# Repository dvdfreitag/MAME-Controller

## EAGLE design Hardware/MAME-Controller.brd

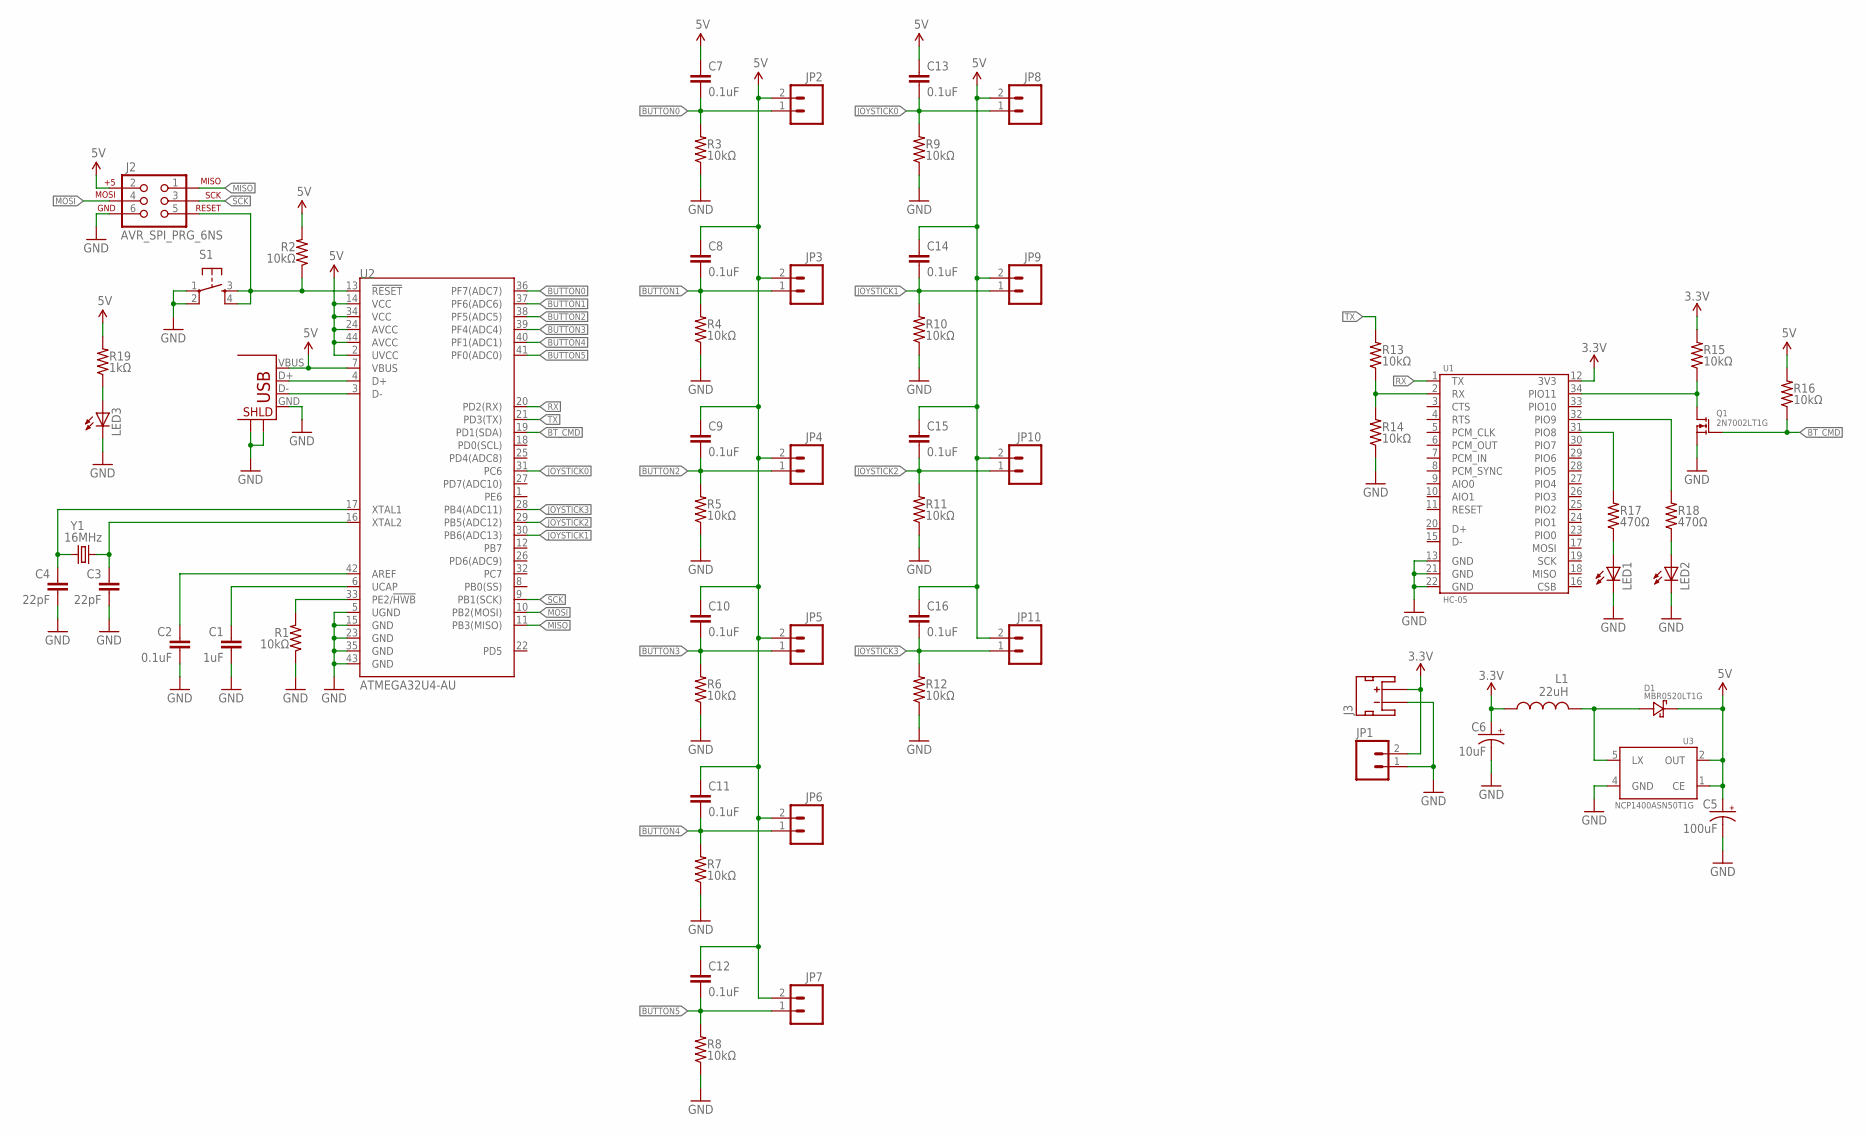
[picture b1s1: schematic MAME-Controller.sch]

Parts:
C1: 1uF; 0805
C2, C7, C8, C9, C10, C11, C12, C13, C14, C15, C16: 0.1uF; 0805
C3, C4: 22pF; 0805
C5: 100uF; CAP_POL-0.35X0.5
C6: 10uF; EIA3216-KIT
D1: MBR0520LT1G; SOD123
J1: USB+SHIELD; USB-B-PTH
J2: AVR_SPI_PRG_6NS; 2X3-NS
J3: JST_2MM_MALE; JST-2-SMD
JP1: M02PTH; 1X02
JP2, JP3, JP4, JP5, JP6, JP7, JP8, JP9, JP10, JP11: M02POLAR; MOLEX-1X2
L1: 22uH; 0805
LED1, LED2, LED3: LED-FKIT-1206; FKIT-LED-1206
Q1: 2N7002LT1G; SOT23
R1, R2, R3, R4, R5, R6, R7, R8, R9, R10, R11, R12, R13, R14, R15, R16: 10kΩ; 0805
R17, R18: 470Ω; 0805
R19: 1kΩ; 0805
S1: TAC_SWITCHSMD; TACTILE_SWITCH_SMD
U1: HC-05
U2: ATMEGA32U4-AU; TQFP-44
U3: NCP1400ASN50T1G; SOT23-5
Y1: 16MHz; HC49US

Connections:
3.3V: C6.A (+), J3.2 (+), JP1.2, L1.2, R15.2, U1.12 (3V3)
5V: C5.+, C7.1, C8.1, C9.1, C10.1, C11.1, C12.1, C13.1, C14.1, C15.1, C16.1, D1.CATHODE (C), J1.VBUS, J2.2, JP2.2, JP3.2, JP4.2, JP5.2, JP6.2, JP7.2, JP8.2, JP9.2, JP10.2, JP11.2, R2.2, R16.2, R19.2, U2.2 (UVCC), U2.7 (VBUS), U2.14 (VCC), U2.24 (AVCC), U2.34 (VCC), U2.44 (AVCC), U3.1 (CE), U3.2 (OUT)
BT_CMD: Q1.1 (GATE), R16.1, U2.19 (PD1(SDA))
BUTTON0: C7.2, JP2.1, R3.2, U2.36 (PF7(ADC7))
BUTTON1: C8.2, JP3.1, R4.2, U2.37 (PF6(ADC6))
BUTTON2: C9.2, JP4.1, R5.2, U2.38 (PF5(ADC5))
BUTTON3: C10.2, JP5.1, R6.2, U2.39 (PF4(ADC4))
BUTTON4: C11.2, JP6.1, R7.2, U2.40 (PF1(ADC1))
BUTTON5: C12.2, JP7.1, R8.2, U2.41 (PF0(ADC0))
D_N: J1.D-, U2.3 (D-)
D_P: J1.D+, U2.4 (D+)
GND: C1.2, C2.2, C3.2, C4.2, C5.-, C6.C (-), J1.GND, J1.S1, J1.S2, J2.6, J3.1 (-), JP1.1, LED1.C, LED2.C, LED3.C, Q1.2 (SOURCE), R1.1, R3.1, R4.1, R5.1, R6.1, R7.1, R8.1, R9.1, R10.1, R11.1, R12.1, R14.1, S1.1, S1.2, U1.13 (GND), U1.21 (GND), U1.22 (GND), U2.5 (UGND), U2.15 (GND), U2.23 (GND), U2.35 (GND), U2.43 (GND), U3.4 (GND)
JOYSTICK0: C13.2, JP8.1, R9.2, U2.31 (PC6)
JOYSTICK1: C14.2, JP9.1, R10.2, U2.30 (PB6(ADC13))
JOYSTICK2: C15.2, JP10.1, R11.2, U2.29 (PB5(ADC12))
JOYSTICK3: C16.2, JP11.1, R12.2, U2.28 (PB4(ADC11))
MISO: J2.1, U2.11 (PB3(MISO))
MOSI: J2.4, U2.10 (PB2(MOSI))
unnamed: R1.2, U2.33 (PE2/!HWB)
unnamed: C1.1, U2.6 (UCAP)
unnamed: C2.1, U2.42 (AREF)
unnamed: C4.1, U2.17 (XTAL1), Y1.1
unnamed: C3.1, U2.16 (XTAL2), Y1.2
unnamed: J2.5, R2.1, S1.3, S1.4, U2.13 (!RESET)
unnamed: D1.ANODE (A), L1.1, U3.5 (LX)
unnamed: R13.1, R14.2, U1.2 (RX)
unnamed: R17.2, U1.31 (PIO8)
unnamed: R18.2, U1.32 (PIO9)
unnamed: Q1.3 (DRAIN), R15.1, U1.34 (PIO11)
unnamed: LED2.A, R18.1
unnamed: LED1.A, R17.1
unnamed: LED3.A, R19.1
RX: U1.1 (TX), U2.20 (PD2(RX))
SCK: J2.3, U2.9 (PB1(SCK))
TX: R13.2, U2.21 (PD3(TX))

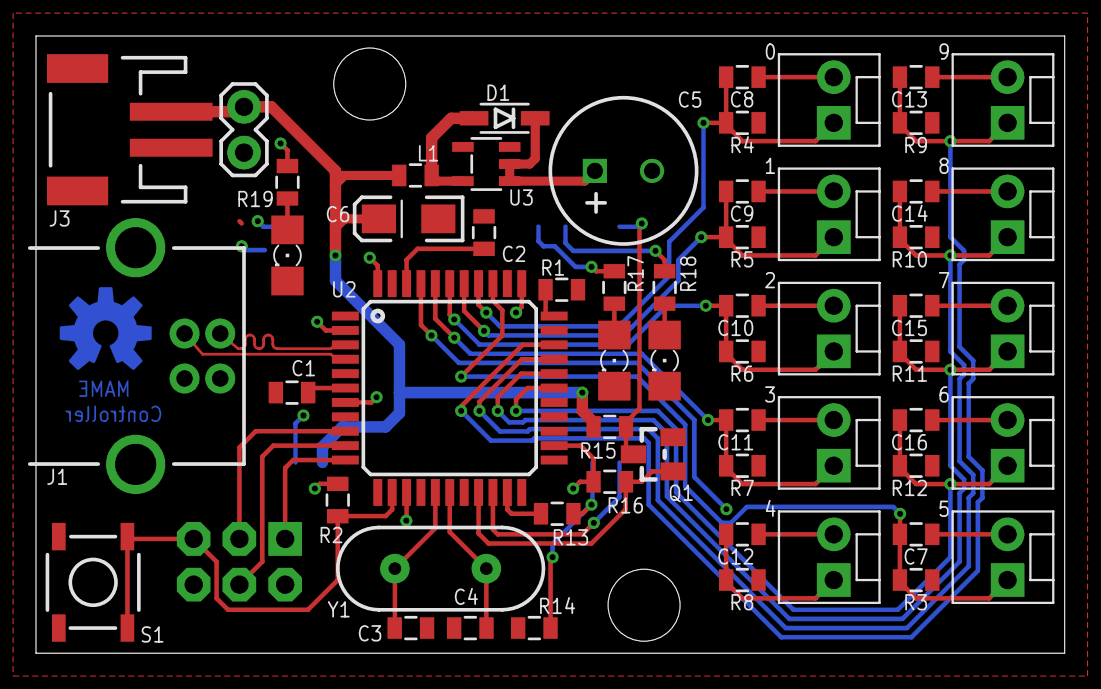
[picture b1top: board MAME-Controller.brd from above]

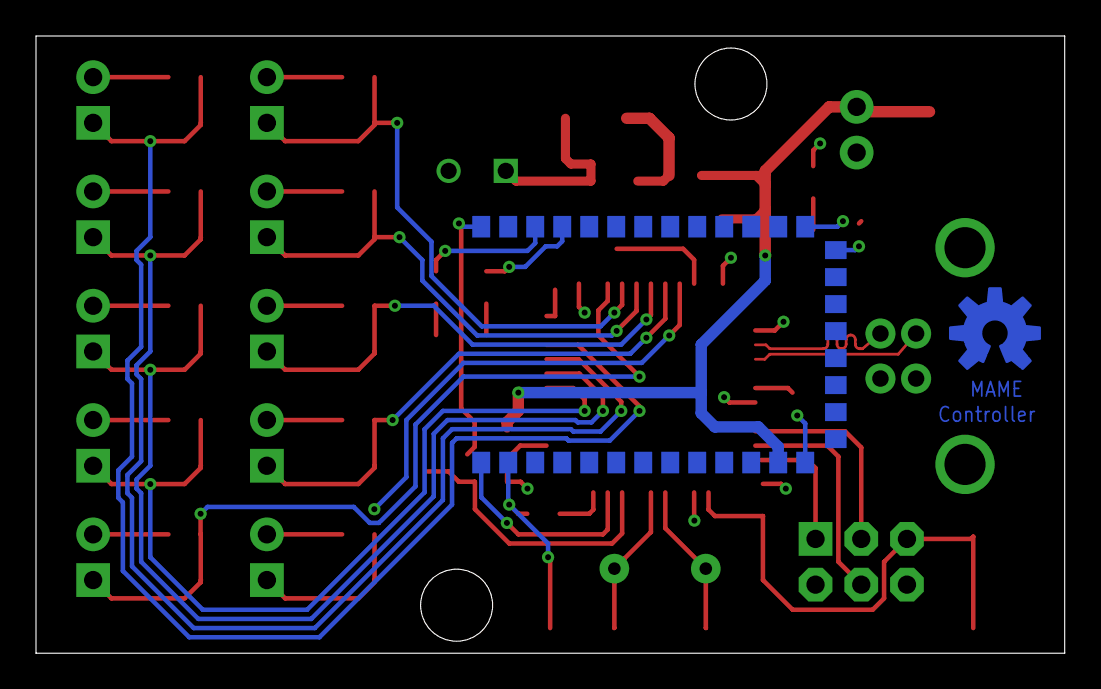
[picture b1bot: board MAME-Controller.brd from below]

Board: 2 copper layers, 57.1 x 34.3 mm, 61 parts (2 on the bottom side), 35 nets.

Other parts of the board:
U$1: OSHW-LOGO-M-TOP

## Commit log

2015-05-03 Initial commit
    Added hardware files
2015-05-04 Added software
    Added arduino control code

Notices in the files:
parts and their libraries:
SparkFun-Passives: Licensing: CC v3.0 Share-Alike You are welcome to use this library for commercial purposes.
